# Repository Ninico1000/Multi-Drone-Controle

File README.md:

# Multi-Drone Mission Planner

A React-based mission planning system for controlling multiple drones using a 10-anchor BLE AoA positioning system with 0.1-0.3m accuracy.

## Features

- **3D Visualization**: Interactive Three.js scene with 25x25m flight area
- **10-Anchor BLE AoA System**: High-precision positioning
- **Keyframe-Based Missions**: Timeline editor with smooth/linear interpolation
- **Multi-Drone Support**: Control up to 3 drones simultaneously
- **Arduino Code Generation**: Automatic generation of PID-controlled flight code
- **Formation Flying**: Preset formations (circle, line, triangle)
- **Mission Save/Load**: JSON-based mission storage
- **Emergency Stop**: Safety features for immediate landing

## Project Structure

```
Multi Drone Control/
├── public/
│   └── index.html              # HTML entry point
├── src/
│   ├── components/
│   │   ├── MultiDroneControl.jsx    # Main component with state management
│   │   ├── ThreeScene.jsx           # 3D visualization using Three.js
│   │   ├── DronePanel.jsx           # Drone status sidebar
│   │   ├── AnchorSetup.jsx          # Anchor configuration panel
│   │   ├── KeyframeEditor.jsx       # Keyframe editor component
│   │   ├── Timeline.jsx             # Timeline visualization
│   │   └── EventLog.jsx             # Event logging component
│   ├── constants/
│   │   └── defaults.js              # Default configurations and constants
│   ├── utils/
│   │   ├── interpolation.js         # Interpolation functions
│   │   ├── arduinoCodeGenerator.js  # Arduino code generation
│   │   └── fileOperations.js        # Mission save/load operations
│   ├── App.js                       # App component
│   ├── index.js                     # React entry point
│   └── index.css                    # Global styles with Tailwind
├── package.json                     # Dependencies and scripts
├── tailwind.config.js               # Tailwind CSS configuration
└── postcss.config.js                # PostCSS configuration
```

## Quick Start

**New Setup with ESP32 Access Point (Recommended):**

1. **Flash ESP32 Access Point** (`AccessPoint_ESP32.ino`)
2. **Flash ESP32 Drones** (`DroneControl.txt`)
3. **Connect ESP32 AP to PC** via USB
4. **Install dependencies** and run:

```bash
# Terminal 1: Bridge Server
cd server
npm install
npm start

# Terminal 2: React App
npm install
npm start
```

5. **Power on drones** - they auto-connect to ESP32 AP
6. **Click "Drohnen suchen"** in the web app
7. **Start flying!**

📖 **See [SETUP_GUIDE.md](SETUP_GUIDE.md) for detailed installation instructions**

## Installation

### 1. Install React App Dependencies
```bash
npm install
```

### 2. Install Bridge Server Dependencies
```bash
cd server
npm install
cd ..
```

## System Architecture

### Option 1: ESP32 Access Point (Recommended)

```
PC → USB → ESP32 AP → WiFi → Drones
```

- **ESP32 Access Point** creates dedicated WiFi network
- **Auto-discovers** drones on the network
- **Serial/USB** bridge for PC communication
- **No WiFi required** on PC

### Option 2: Direct UDP (Legacy)

```
PC → WiFi → Drones
```

- Requires PC with WiFi
- Manual IP configuration
- Use `npm run start:udp` in server folder

## Building for Production

```bash
npm run build
```

This creates an optimized production build in the `build/` directory.

## Usage

### 1. Check Bridge Status

Look for the **"Bridge OK"** indicator (green) in the top-right of the Drone Panel. If it shows "No Bridge" (red), make sure the bridge server is running.

### 2. Connect Drones

1. Click the WiFi icon next to each drone to mark it as "connected"
2. Verify the drone's IP address matches your ESP32 configuration
3. The position will update in real-time via telemetry once the drone is online

### 3. Create Missions

1. Click **"+ KF"** (Keyframe) to add waypoints for a drone
2. Edit keyframe parameters in the Keyframe Editor:
   - **Time**: When to reach this waypoint (seconds)
   - **X, Y, Z**: Position in meters
   - **Yaw, Pitch, Roll**: Orientation in degrees
3. Use formation presets for synchronized multi-drone patterns:
   - **Kreis**: Circle formation
   - **Linie**: Line formation

### 4. Upload Mission to Drone

1. Click **"Upload"** to send the mission to the ESP32 via WiFi/UDP
2. The drone will receive and store all keyframes
3. Check the Event Log for confirmation

### 5. Mission Control

Once uploaded, control the drone's mission execution:
- **Start**: Begin autonomous mission execution
- **Stop**: Pause/stop the current mission
- **E-Stop**: Emergency stop (immediate landing)

### 6. Live Simulation

Use the **"Play"** button in the main viewport to simulate missions locally without sending to drones. This is useful for testing and visualization.

### 7. Mission Management

- **Speichern**: Export mission as JSON file
- **Laden**: Import previously saved missions
- Missions include all keyframes, interpolation settings, and anchor configuration

## Communication Architecture

### Serial Bridge Mode (Default)

```
React Web App (Browser)
      ↓ WebSocket (port 3001)
Node.js Bridge Server
      ↓ Serial/USB (115200 baud, JSON)
ESP32 Access Point (192.168.4.1)
      ↓ WiFi UDP (ports 8888/8889)
ESP32 Drones (192.168.4.2+)
      ↑ Telemetry (10Hz, JSON)
```

### Protocols

#### 1. WebSocket (React ↔ Bridge Server)

**Commands from React:**
```json
{
  "command": "discover"  // Find drones
}
{
  "droneIP": "192.168.4.2",
  "payload": {"cmd": "mission", "data": [...]}
}
```

**Responses to React:**
```json
{
  "type": "drone_list",
  "drones": [{"ip": "192.168.4.2", "name": "Drone-01"}]
}
{
  "type": "telemetry",
  "droneIP": "192.168.4.2",
  "data": {"x": 1.5, "y": 2.3, "z": 2.1, ...}
}
```

#### 2. Serial (Bridge Server ↔ ESP32 AP)

**Commands to ESP32 AP:**
```json
{"cmd": "discover"}
{"cmd": "send", "ip": "192.168.4.2", "data": {...}}
{"cmd": "list"}
```

**Responses from ESP32 AP:**
```json
{"type": "drone_list", "drones": [...]}
{"type": "telemetry", "ip": "192.168.4.2", "data": {...}}
{"type": "drone_connected", "ip": "192.168.4.2"}
```

#### 3. WiFi UDP (ESP32 AP ↔ Drones)

**Commands to drones (port 8888):**
```json
{"cmd": "mission", "data": [{"t":0, "x":0, "y":0, "z":2, ...}, ...]}
{"cmd": "start"}
{"cmd": "stop"}
{"cmd": "emergency"}
```

**Telemetry from drones (port 8889, 10Hz):**
```json
{
  "x": 1.5, "y": 2.3, "z": 2.1,
  "yaw": 45.0, "pitch": 5.2, "roll": -2.1,
  "tx": 3.0, "ty": 3.0, "tz": 3.0
}
```

## Tech Stack

- **React** 18.2.0 - UI framework
- **Three.js** 0.158.0 - 3D graphics
- **Lucide React** - Icon library
- **Tailwind CSS** - Styling
- **Node.js + WebSocket (ws)** - Bridge server
- **UDP** - Drone communication protocol

## Hardware Requirements

- **ESP32 Mini** with built-in OLED display (128x64)
- **MPU6050** Gyro/Accelerometer
- **BLE 5.1** module for AoA positioning
- **10 BLE Anchors** for positioning system
- **Betaflight Flight Controller** (SBUS input)

## License

This project is for educational and research purposes.

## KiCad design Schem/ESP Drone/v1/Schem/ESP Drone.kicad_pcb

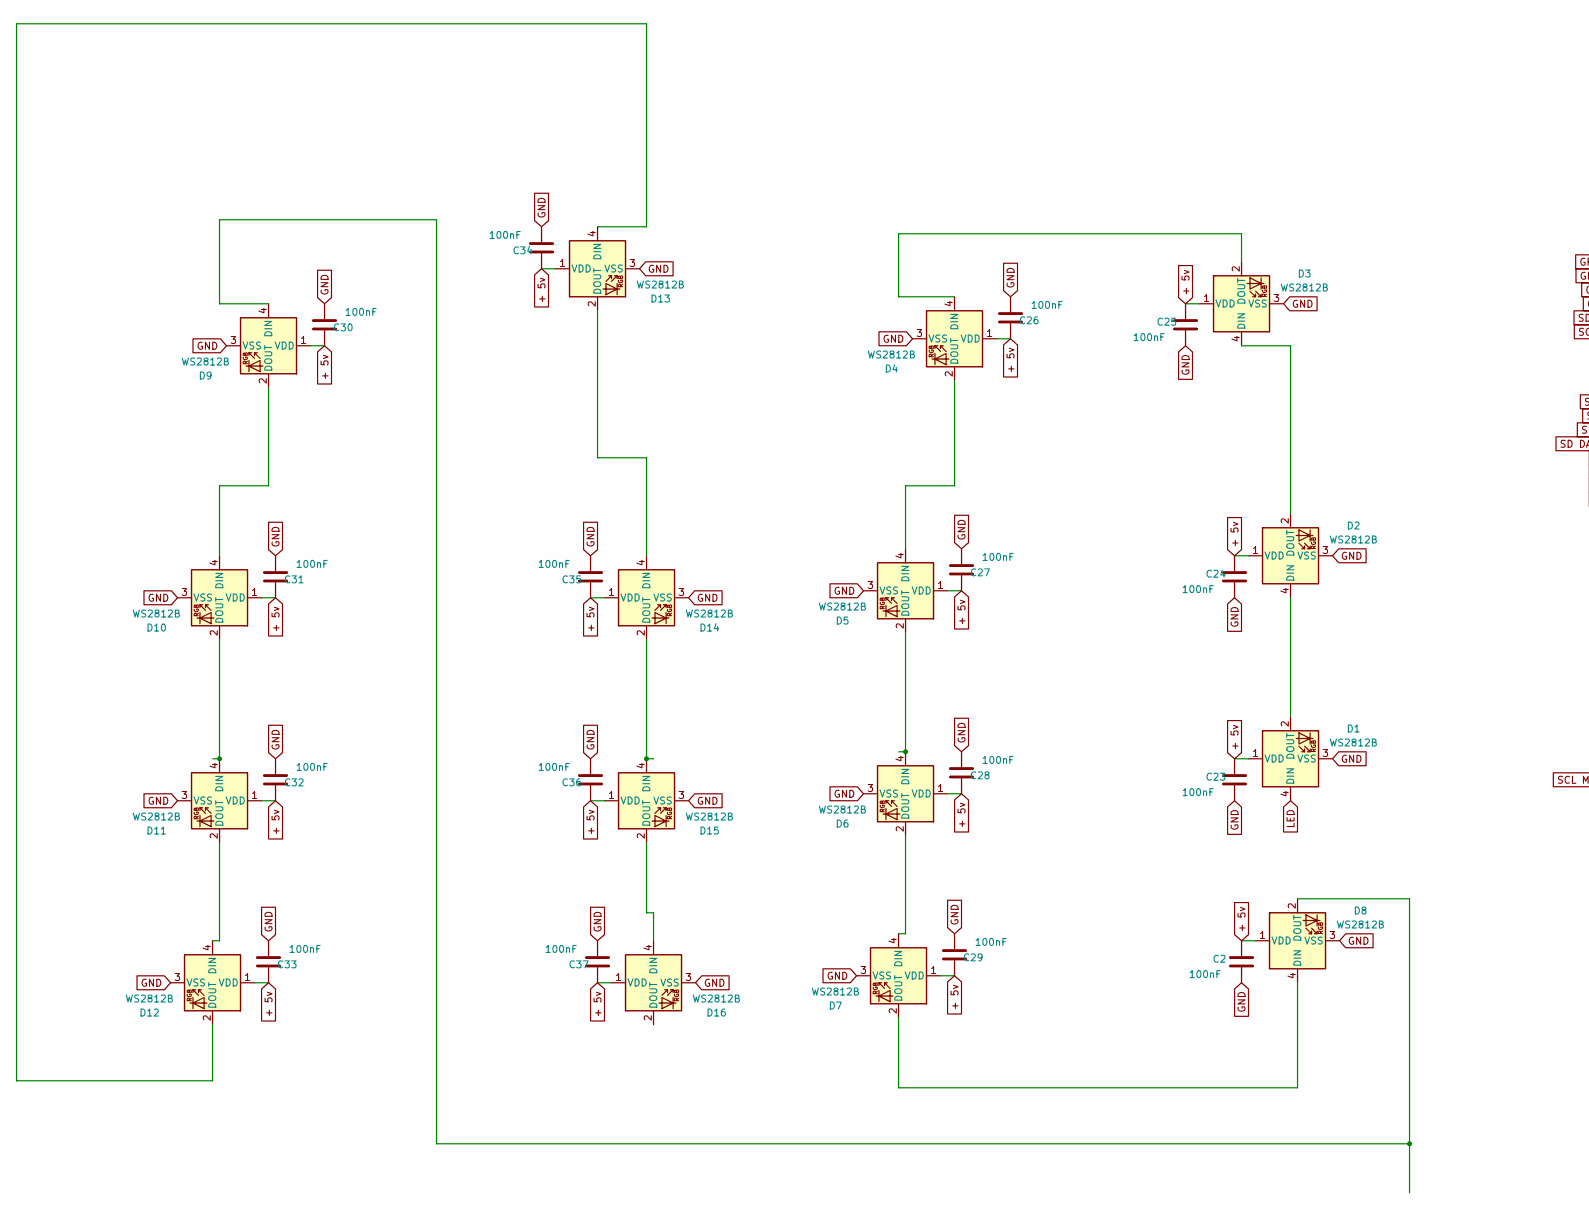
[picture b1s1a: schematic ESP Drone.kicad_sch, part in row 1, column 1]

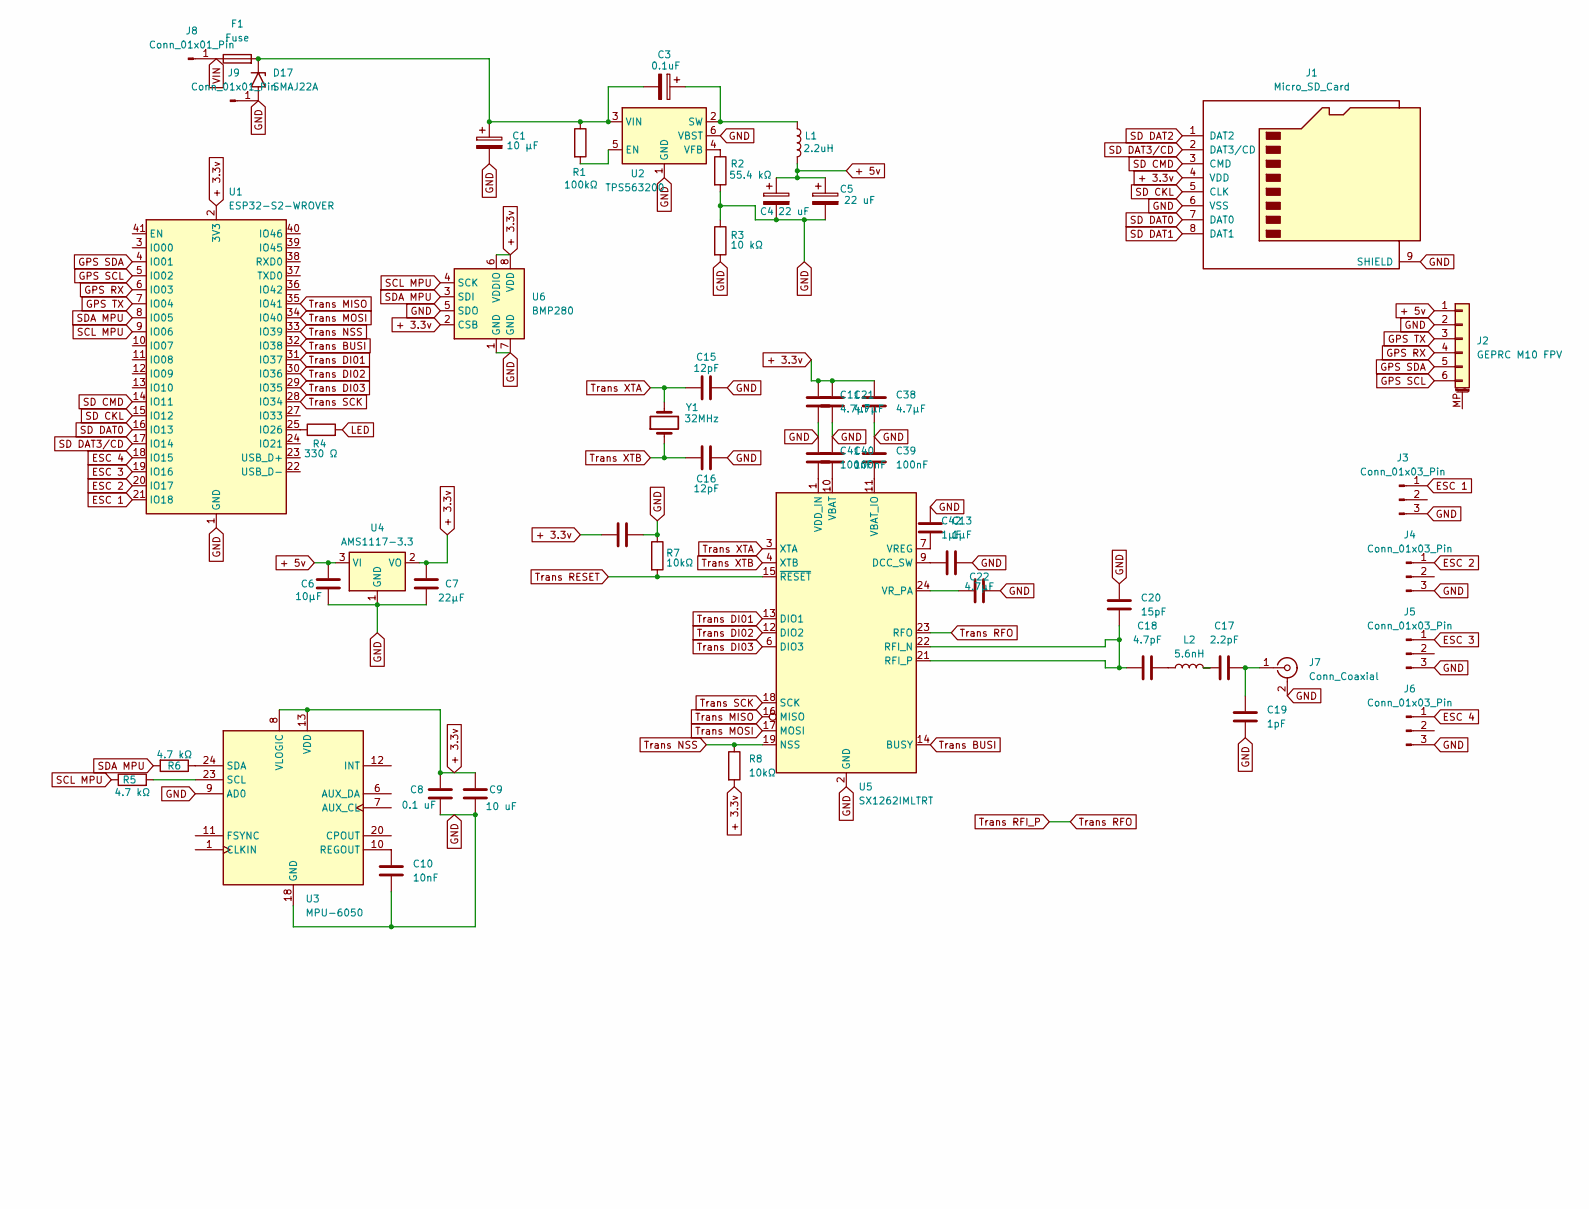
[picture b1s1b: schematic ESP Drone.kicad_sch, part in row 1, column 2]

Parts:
C1: 10 µF; C_1206_3216Metric
C2, C14, C23, C24, C25, C26, C27, C28, C29, C30, C31, C32, C33, C34, C35, C36, C37, C39, C40, C41: 100nF; C_0603_1608Metric
C3: 0.1uF; C_0603_1608Metric
C4, C5: 22 uF; C_1206_3216Metric
C6: 10µF; C_1206_3216Metric
C7: 22µF; C_1206_3216Metric
C8: 0.1 uF; C_0603_1608Metric
C9: 10 uF; C_1206_3216Metric
C10: 10nF; C_0603_1608Metric
C11, C21, C22, C38: 4.7µF; C_1206_3216Metric
C13, C42: 1µF; C_1206_3216Metric
C15, C16: 12pF; C_0603_1608Metric
C17: 2.2pF; C_0603_1608Metric
C18: 4.7pF; C_0603_1608Metric
C19: 1pF; C_0603_1608Metric
C20: 15pF; C_0603_1608Metric
D1, D2, D3, D4, D5, D6, D7, D8, D9, D10, D11, D12, D13, D14, D15, D16: WS2812B; LED_WS2812B_PLCC4_5.0x5.0mm_P3.2mm
D17: SMAJ22A; D_SMA
F1: Fuse; Fuseholder_Blade_Mini_Keystone_3568
J1: Micro_SD_Card; microSD_HC_Molex_104031-0811
J2: GEPRC M10 FPV; JST_EH_B6B-EH-A_1x06_P2.50mm_Vertical
J3, J4, J5, J6: Conn_01x03_Pin; JST_EH_B3B-EH-A_1x03_P2.50mm_Vertical
J7: Conn_Coaxial; U.FL_Hirose_U.FL-R-SMT-1_Vertical
J8, J9: Conn_01x01_Pin; high power throu hole
L1: 2.2uH; L_1210_3225Metric
L2: 5.6nH; L_0805_2012Metric
R1: 100kΩ; R_0201_0603Metric
R2: 55.4 kΩ; R_0201_0603Metric
R3: 10 kΩ; R_0201_0603Metric
R4: 330 Ω; R_0201_0603Metric
R5, R6: 4.7 kΩ; R_0201_0603Metric
R7, R8: 10kΩ; R_0201_0603Metric
U1: ESP32-S2-WROVER; ESP32-DevKitC
U2: TPS563200; SOT-23-6
U3: MPU-6050; InvenSense_QFN-24_4x4mm_P0.5mm
U4: AMS1117-3.3; SOT-223-3_TabPin2
U5: SX1262IMLTRT; QFN-24-1EP_4x4mm_P0.5mm_EP2.6x2.6mm
U6: BMP280; Bosch_LGA-8_2x2.5mm_P0.65mm_ClockwisePinNumbering
Y1: 32MHz; Crystal_HC49-U_Horizontal

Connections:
+ 3.3v: C7.1, C8.2, C9.2, C11.1, C14.2, C21.1, C38.1, J1.4 (VDD), R8.2, U1.2 (3V3), U3.8 (VLOGIC), U3.13 (VDD), U4.2 (VO), U6.2 (CSB), U6.6 (VDDIO), U6.8 (VDD)
+ 5v: C2.1, C4.1, C5.1, C6.1, C23.1, C24.1, C25.1, C26.1, C27.1, C28.1, C29.1, C30.1, C31.1, C32.1, C33.1, C34.1, C35.1, C36.1, C37.1, D1.1 (VDD), D2.1 (VDD), D3.1 (VDD), D4.1 (VDD), D5.1 (VDD), D6.1 (VDD), D7.1 (VDD), D8.1 (VDD), D9.1 (VDD), D10.1 (VDD), D11.1 (VDD), D12.1 (VDD), D13.1 (VDD), D14.1 (VDD), D15.1 (VDD), D16.1 (VDD), J2.1, L1.2, U4.3 (VI)
ESC 1: J3.1, U1.21 (IO18)
ESC 2: J4.1, U1.20 (IO17)
ESC 3: J5.1, U1.19 (IO16)
ESC 4: J6.1, U1.18 (IO15)
GND: C1.2, C2.2, C4.2, C5.2, C6.2, C7.2, C8.1, C9.1, C10.2, C11.2, C13.1, C14.1, C15.2, C16.2, C19.2, C20.1, C21.2, C22.2, C23.2, C24.2, C25.2, C26.2, C27.2, C28.2, C29.2, C30.2, C31.2, C32.2, C33.2, C34.2, C35.2, C36.2, C37.2, C38.2, C39.1, C40.1, C41.1, C42.2, D1.3 (VSS), D2.3 (VSS), D3.3 (VSS), D4.3 (VSS), D5.3 (VSS), D6.3 (VSS), D7.3 (VSS), D8.3 (VSS), D9.3 (VSS), D10.3 (VSS), D11.3 (VSS), D12.3 (VSS), D13.3 (VSS), D14.3 (VSS), D15.3 (VSS), D16.3 (VSS), D17.2 (A2), J1.6 (VSS), J1.9 (SHIELD), J2.2, J3.3, J4.3, J5.3, J6.3, J7.2 (Ext), J9.1 (Pin_1_1), R2.2, R3.1, R3.2, R7.1, U1.1 (GND), U1.26 (GND), U1.42 (GND), U1.43 (GND), U2.1 (GND), U2.6 (VBST), U3.9 (AD0), U3.18 (GND), U4.1 (GND), U5.2 (GND), U5.5 (GND), U5.8 (GND), U5.20 (GND), U5.25 (GND), U6.1 (GND), U6.5 (SDO), U6.7 (GND)
GPS RX: J2.4, U1.6 (IO03)
GPS SCL: J2.6, U1.5 (IO02)
GPS SDA: J2.5, U1.4 (IO01)
GPS TX: J2.3, U1.7 (IO04)
LED: D1.4 (DIN), R4.2
unnamed: C17.2, L2.2
unnamed: C18.2, L2.1
unnamed: D1.2 (DOUT), D2.4 (DIN)
unnamed: D2.2 (DOUT), D3.4 (DIN)
unnamed: D3.2 (DOUT), D4.4 (DIN)
unnamed: D4.2 (DOUT), D5.4 (DIN)
unnamed: D5.2 (DOUT), D6.4 (DIN)
unnamed: D6.2 (DOUT), D7.4 (DIN)
unnamed: D7.2 (DOUT), D8.4 (DIN)
unnamed: D8.2 (DOUT), D9.4 (DIN)
unnamed: D9.2 (DOUT), D10.4 (DIN)
unnamed: D10.2 (DOUT), D11.4 (DIN)
unnamed: D11.2 (DOUT), D12.4 (DIN)
unnamed: D12.2 (DOUT), D13.4 (DIN)
unnamed: D13.2 (DOUT), D14.4 (DIN)
unnamed: D14.2 (DOUT), D15.4 (DIN)
unnamed: D15.2 (DOUT), D16.4 (DIN)
unnamed: C1.1, C3.2, D17.1 (A1), F1.2, R1.1, U2.3 (VIN)
unnamed: C17.1, C19.1, J7.1 (In)
unnamed: R4.1, U1.25 (IO26)
unnamed: R1.2, U2.5 (EN)
unnamed: C3.1, L1.1, U2.2 (SW)
unnamed: R2.1, U2.4 (VFB)
unnamed: C10.1, U3.10 (REGOUT)
unnamed: R5.2, U3.23 (SCL)
unnamed: R6.1, U3.24 (SDA)
unnamed: C42.1, U5.9 (DCC_SW)
unnamed: C18.1, C20.2, U5.21 (RFI_P), U5.22 (RFI_N)
unnamed: C40.2, U5.10 (VBAT)
unnamed: C39.2, U5.11 (VBAT_IO)
unnamed: C41.2, U5.1 (VDD_IN)
unnamed: C13.2, U5.7 (VREG)
unnamed: C22.1, U5.24 (VR_PA)
SCL MPU: R5.1, U1.9 (IO06), U6.4 (SCK)
SD CKL: J1.5 (CLK), U1.15 (IO12)
SD CMD: J1.3 (CMD), U1.14 (IO11)
SD DAT0: J1.7 (DAT0), U1.16 (IO13)
SD DAT1: J1.8 (DAT1)
SD DAT2: J1.1 (DAT2)
SD DAT3/CD: J1.2 (DAT3/CD), U1.17 (IO14)
SDA MPU: R6.2, U1.8 (IO05), U6.3 (SDI)
Trans BUSI: U1.32 (IO38), U5.14 (BUSY)
Trans DI01: U1.31 (IO37), U5.13 (DIO1)
Trans DI02: U1.30 (IO36), U5.12 (DIO2)
Trans DI03: U1.29 (IO35), U5.6 (DIO3)
Trans MISO: U1.35 (IO41), U5.16 (MISO)
Trans MOSI: U1.34 (IO40), U5.17 (MOSI)
Trans NSS: R8.1, U1.33 (IO39), U5.19 (NSS)
Trans RESET: R7.2, U5.15 (~RESET)
Trans RFI_P: U5.23 (RFO)
Trans SCK: U1.28 (IO34), U5.18 (SCK)
Trans XTA: C15.1, U5.3 (XTA), Y1.2
Trans XTB: C16.1, U5.4 (XTB), Y1.1
VIN: F1.1, J8.1 (Pin_1_1)

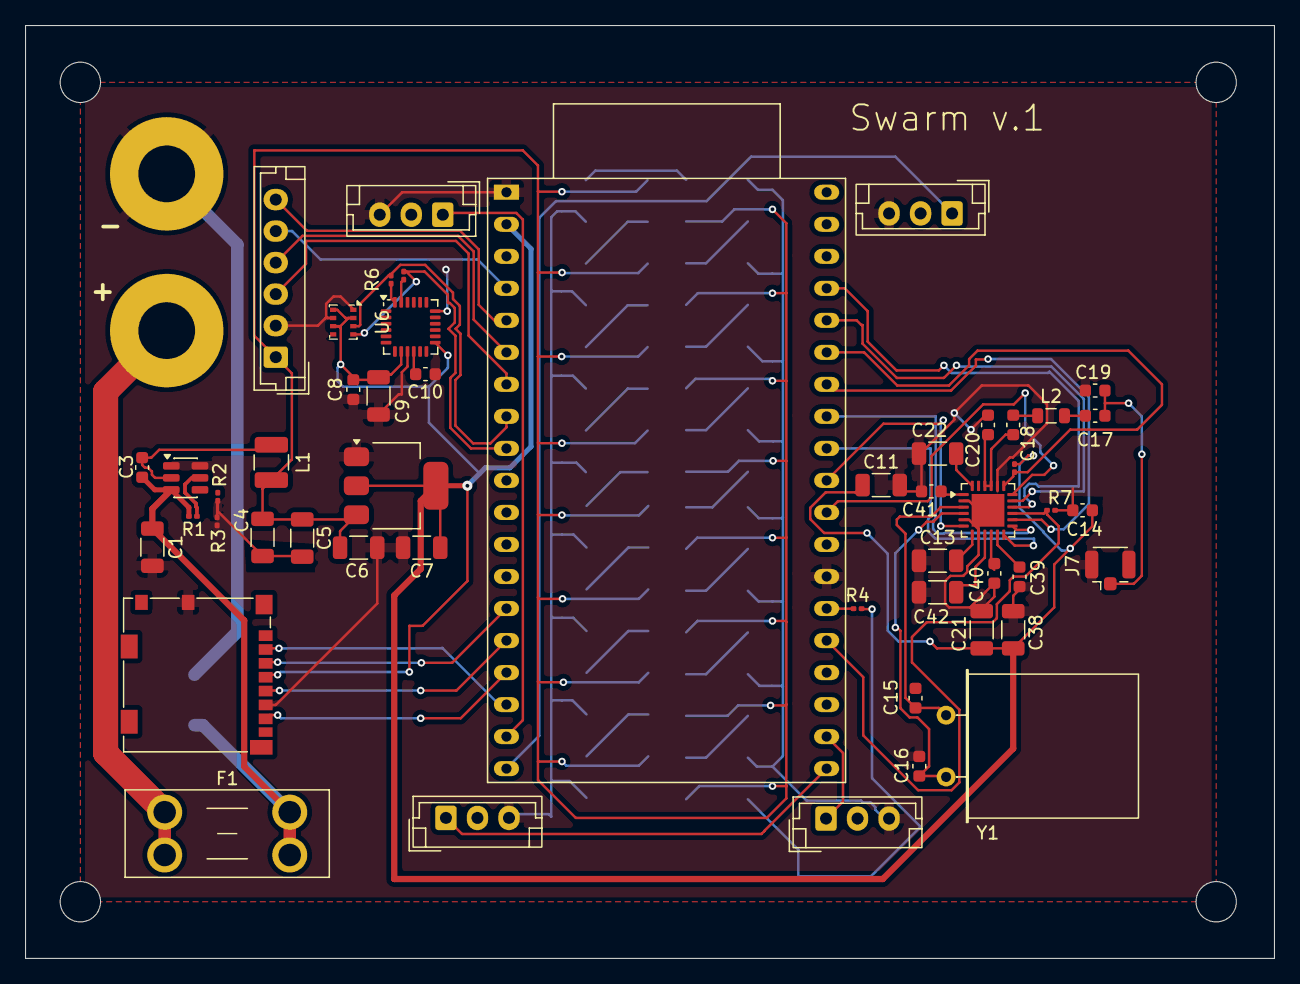
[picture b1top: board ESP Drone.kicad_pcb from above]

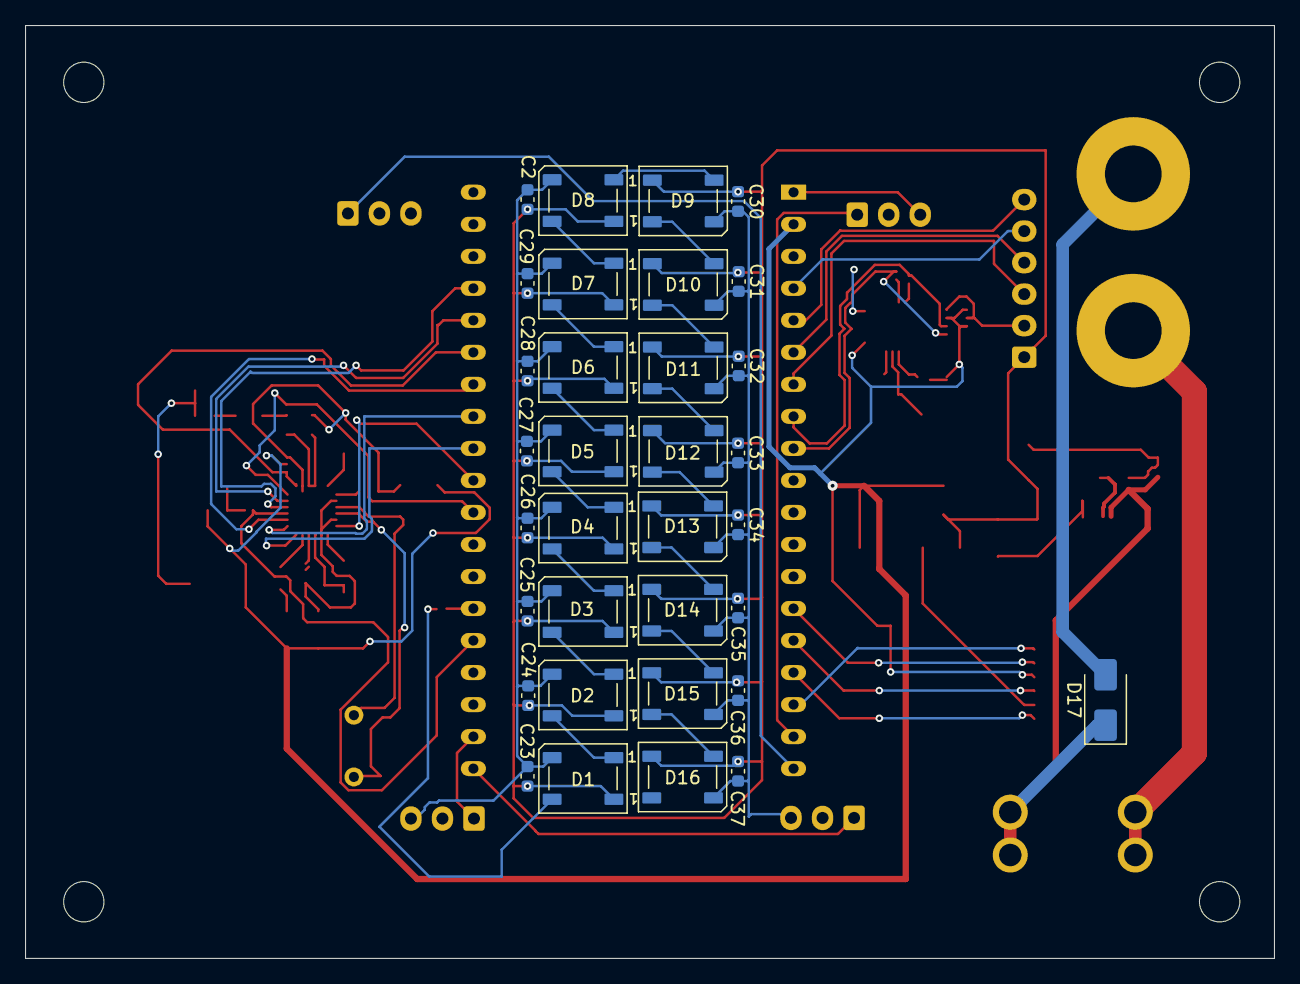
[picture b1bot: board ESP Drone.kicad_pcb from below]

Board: 2 copper layers, 99.1 x 74.0 mm, 85 parts (33 on the bottom side), 63 nets.

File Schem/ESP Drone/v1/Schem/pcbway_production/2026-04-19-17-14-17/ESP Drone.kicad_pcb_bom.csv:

Designator,Quantity,Value,Footprint,Package,MPN,DNP,Mount_Type,Description
C1,1,10 µF,C_1206_3216Metric,,,,smt,Polarized capacitor
C10,1,10nF,C_0603_1608Metric,,,,smt,Unpolarized capacitor
"C11, C21, C22, C38",4,4.7µF,C_1206_3216Metric,,,,smt,Unpolarized capacitor
"C13, C42",2,1µF,C_1206_3216Metric,,,,smt,Unpolarized capacitor
"C14, C2, C23, C24, C25, C26, C27, C28, C29, C30, C31, C32, C33, C34, C35, C36, C37, C39, C40, C41",20,100nF,C_0603_1608Metric,,,,smt,Unpolarized capacitor
"C15, C16",2,12pF,C_0603_1608Metric,,,,smt,Unpolarized capacitor
C17,1,2.2pF,C_0603_1608Metric,,,,smt,Unpolarized capacitor
C18,1,4.7pF,C_0603_1608Metric,,,,smt,Unpolarized capacitor
C19,1,1pF,C_0603_1608Metric,,,,smt,Unpolarized capacitor
C20,1,15pF,C_0603_1608Metric,,,,smt,Unpolarized capacitor
C3,1,0.1uF,C_0603_1608Metric,,,,smt,Polarized capacitor
"C4, C5",2,22 uF,C_1206_3216Metric,,,,smt,Polarized capacitor
C6,1,10µF,C_1206_3216Metric,,,,smt,Unpolarized capacitor
C7,1,22µF,C_1206_3216Metric,,,,smt,Unpolarized capacitor
C8,1,0.1 uF,C_0603_1608Metric,,,,smt,Unpolarized capacitor
C9,1,10 uF,C_1206_3216Metric,,,,smt,Unpolarized capacitor
"D1, D10, D11, D12, D13, D14, D15, D16, D2, D3, D4, D5, D6, D7, D8, D9",16,WS2812B,LED_WS2812B_PLCC4_5.0x5.0mm_P3.2mm,,,,smt,RGB LED with integrated controller
J1,1,Micro_SD_Card,microSD_HC_Molex_104031-0811,,,,smt,Micro SD Card Socket
J2,1,GEPRC M10 FPV,JST_EH_B6B-EH-A_1x06_P2.50mm_Vertical,,,,tht,"Generic connectable mounting pin connector, single row, 01x06, script generated (kicad-library-utils/schlib/autogen/connector/)"
"J3, J4, J5, J6",4,Conn_01x03_Pin,JST_EH_B3B-EH-A_1x03_P2.50mm_Vertical,,,,tht,"Generic connector, single row, 01x03, script generated"
J7,1,Conn_Coaxial,U.FL_Hirose_U.FL-R-SMT-1_Vertical,,,,smt,"coaxial connector (BNC, SMA, SMB, SMC, Cinch/RCA, LEMO, ...)"
L1,1,2.2uH,L_1210_3225Metric,,,,smt,Inductor
L2,1,5.6nH,L_0805_2012Metric,,,,smt,Inductor
R1,1,100kΩ,R_0201_0603Metric,,,,smt,Resistor
R2,1,55.4 kΩ,R_0201_0603Metric,,,,smt,Resistor
R3,1,10 kΩ,R_0201_0603Metric,,,,smt,Resistor
R4,1,330 Ω,R_0201_0603Metric,,,,smt,Resistor
"R5, R6",2,4.7 kΩ,R_0201_0603Metric,,,,smt,Resistor
"R7, R8",2,10kΩ,R_0201_0603Metric,,,,smt,Resistor
U1,1,ESP32-S2-WROVER,ESP32-DevKitC,,,,tht,"RF Module, ESP32-D0WDQ6 SoC, Wi-Fi 802.11b/g/n, 32-bit, 2.7-3.6V, onboard antenna, SMD"
U2,1,TPS563200,SOT-23-6,,,,smt,"3A Synchronous Step-Down Voltage Regulator, Adjustable Output Voltage, 4.5-17V Input Voltage, SOT-23-6"
U3,1,MPU-6050,InvenSense_QFN-24_4x4mm_P0.5mm,,,,smt,"InvenSense 6-Axis Motion Sensor, Gyroscope, Accelerometer, I2C"
U4,1,AMS1117-3.3,SOT-223-3_TabPin2,,,,smt,"1A Low Dropout regulator, positive, 3.3V fixed output, SOT-223"
U5,1,SX1262IMLTRT,QFN-24-1EP_4x4mm_P0.5mm_EP2.6x2.6mm,,,,smt,"150 MHz to 960 MHz Low Power Long Range Transceiver, 22dBm output power, spreading factor from 5 to 12, LoRA, QFN-24"
Y1,1,32MHz,Crystal_HC49-U_Horizontal,,,,tht,Two pin crystal

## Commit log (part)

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2026-04-19 Initial commit: Multi Drone Control project
2026-04-19 Create README.md for Multi-Drone Mission Planner
    Add comprehensive README for Multi-Drone Mission Planner project, detailing features, project structure, installation, usage, communication architecture, tech stack, and hardware requirements.
2026-04-25 feat: BMP280, LoRa-Protokoll, i18n, Blackbox, Pre-flight Check
2026-04-25 Update CHANGELOG in English
2026-05-10 Entferne ungenutzten Code
    - Lösche arduinoCodeGenerator.js (wird nirgendwo importiert)
    - Lösche SystemLauncher.integration.md (guide für nicht existierende Komponente)
    - Entferne DRONE_MODEL_CONFIG aus defaults.js (nirgendwo verwendet)
    - Entferne loadFigureJSON aus fileOperations.js (nirgendwo verwendet)
    - Entferne startMissionAt aus droneConnection.js (nirgendwo aufgerufen)
    - Entferne simplifyVertices + getVerticesBoundingBox aus modelUtils.js (nirgendwo verwendet)
2026-05-10 Füge LoRa Terminal und Funke (Jumper T2 Pro) hinzu
    Server (serial-bridge.js):
    - Port-Registry für mehrere serielle Ports (Rollen: 'ap', 'lora_terminal')
    - HTTP/Express Wrapper auf Port 3001 für REST-Endpoints
    - GET /api/ports — verfügbare COM-Ports auflisten
    - POST /api/ports/connect — Port für eine Rolle öffnen
    - POST /api/ports/disconnect — Port schließen
2026-05-10 simplify: reduce code size and fix subtle bugs
    - FunkeControl: fix stale gamepadIndex closure in disconnect handler via ref;
    add change-detection guard to 50Hz setChannels (prevents idle re-renders);
    extract DRONE_CMDS config array to replace 4 near-identical buttons;
    wrap handleSelectDrone in useCallback
    - PortSelector: remove redundant localBaud state, drive baud rate from prop
    - LoraTerminal: pass onConnect directly instead of unnecessary wrapper arrow
2026-05-10 merge: inline 3 single-consumer files to reduce file count
    - EventLog.jsx (18 lines) → inlined into MultiDroneControl.jsx
    - PortSelector.jsx (71 lines) → inlined into LoraTerminal.jsx
    - App.js (14 lines) → inlined into index.js
    All three files had exactly one consumer each and were too small
    to justify a separate file. No functional change.
    https://claude.ai/code/session_01NuFgtthGHyzajUtW6DuHgV
2026-05-13 Exe installer added
2026-05-14 Desktop Version 2
2026-05-14 Main Programm
